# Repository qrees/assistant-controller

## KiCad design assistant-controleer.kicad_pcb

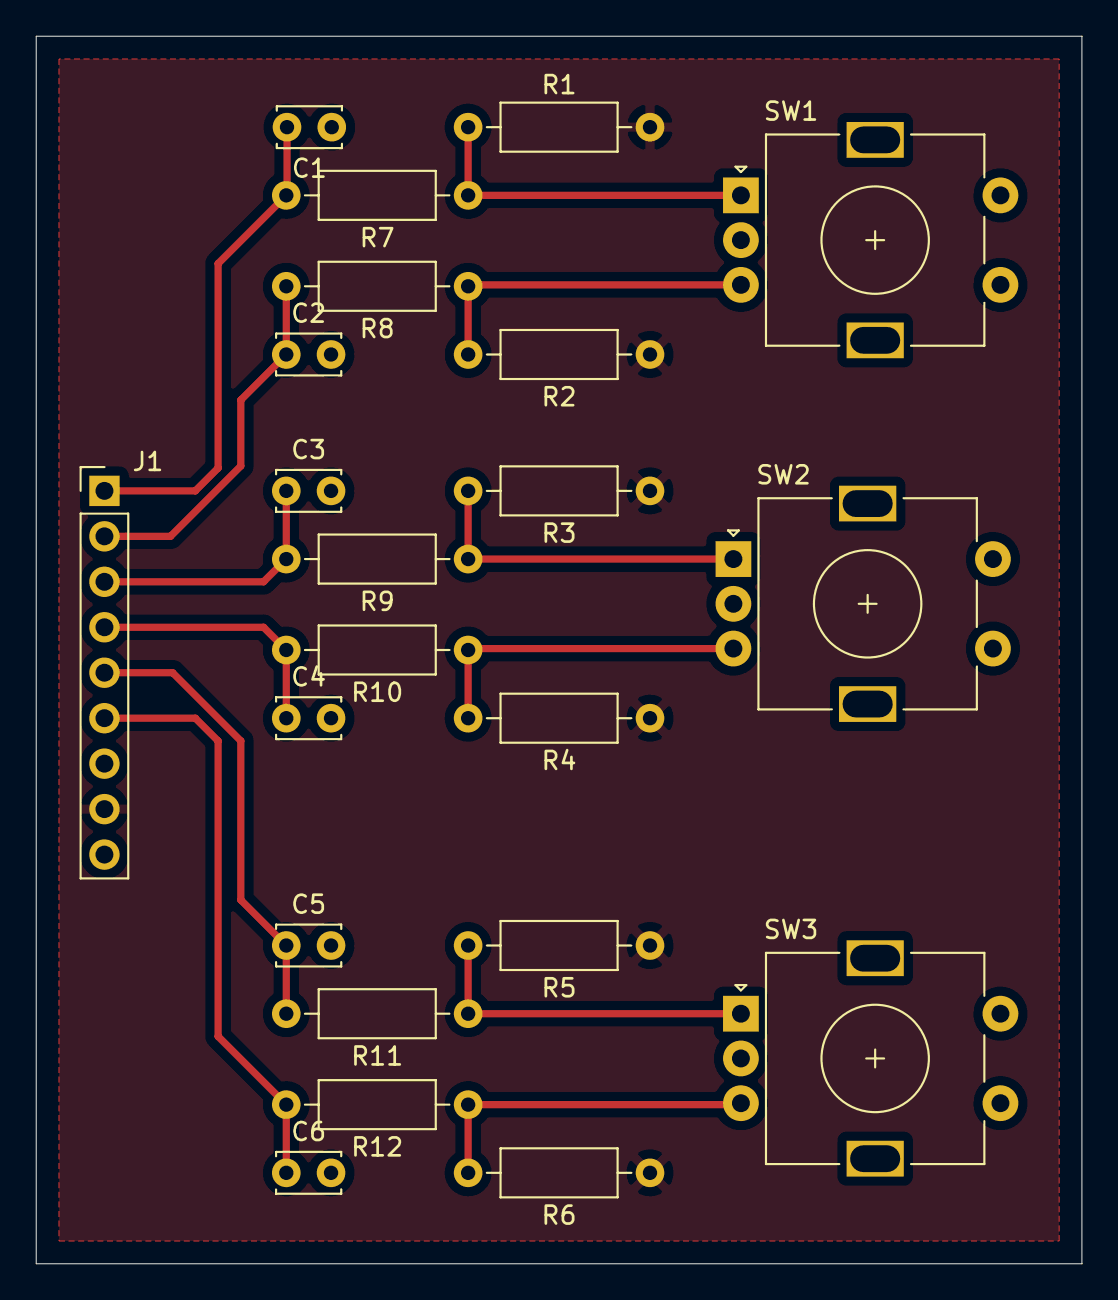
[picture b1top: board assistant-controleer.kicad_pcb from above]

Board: 2 copper layers, 58.4 x 68.6 mm, 22 parts (0 on the bottom side), 14 nets.

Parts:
C1, C2, C3, C4, C5, C6: 10n; C_Disc_D3.4mm_W2.1mm_P2.50mm
J1: Conn_01x09_Male; PinHeader_1x09_P2.54mm_Vertical
R1, R2, R3, R4, R5, R6, R7, R8, R9, R10, R11, R12: 10K; R_Axial_DIN0207_L6.3mm_D2.5mm_P10.16mm_Horizontal
SW1, SW2, SW3: Rotary_Encoder_Switch; RotaryEncoder_Alps_EC11E-Switch_Vertical_H20mm

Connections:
+3V3: J1.8, R1.2, R2.1, R3.1, R4.1, R5.1, R6.1
/enc1_A: R1.1, R7.1, SW1.A
/enc1_B: R2.2, R8.1, SW1.B
/enc2_A: R3.2, R9.1, SW2.A
/enc2_B: R4.2, R10.1, SW2.B
/enc3_A: R5.2, R11.1, SW3.A
/enc3_B: R6.2, R12.1, SW3.B
GND: C1.1, C2.2, C3.2, C4.2, C5.2, C6.2, J1.7, SW1.C, SW2.C, SW3.C
unnamed: C1.2, J1.1, R7.2
unnamed: C2.1, J1.2, R8.2
unnamed: C3.1, J1.3, R9.2
unnamed: C4.1, J1.4, R10.2
unnamed: C5.1, J1.5, R11.2
unnamed: C6.1, J1.6, R12.2
